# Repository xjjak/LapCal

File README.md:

[![CC BY-NC-SA 4.0][cc-by-nc-sa-shield]][cc-by-nc-sa]

# LapCal

*by Emil² - Ξ*

Building gloves that enable typing on a 34-key keyboard without an actual physical keyboard using IMUs and machine learning. 

This work is licensed under a
[Creative Commons Attribution-NonCommercial-ShareAlike 4.0 International License][cc-by-nc-sa].

[![CC BY-NC-SA 4.0][cc-by-nc-sa-image]][cc-by-nc-sa]

[cc-by-nc-sa]: http://creativecommons.org/licenses/by-nc-sa/4.0/
[cc-by-nc-sa-image]: https://licensebuttons.net/l/by-nc-sa/4.0/88x31.png
[cc-by-nc-sa-shield]: https://img.shields.io/badge/License-CC%20BY--NC--SA%204.0-lightgrey.svg

## Attributions

For the ring CAD models in OpenSCAD we use the [Round-Anything library by Irev-Dev](https://github.com/Irev-Dev/Round-Anything), which is licensed under the MIT License.

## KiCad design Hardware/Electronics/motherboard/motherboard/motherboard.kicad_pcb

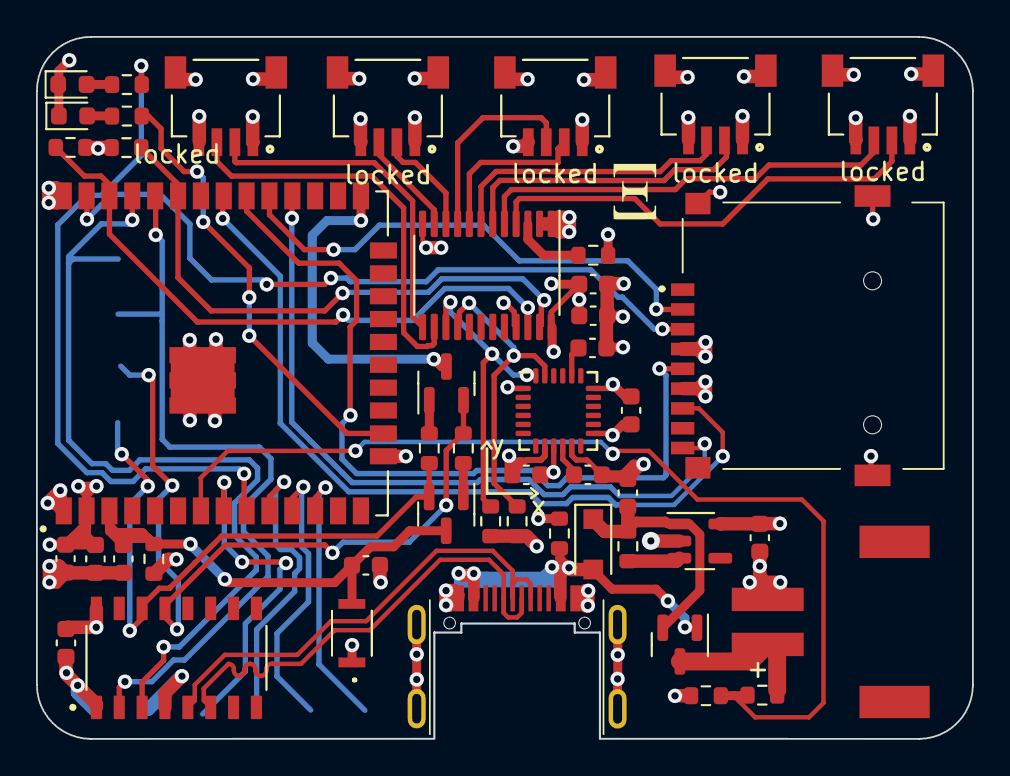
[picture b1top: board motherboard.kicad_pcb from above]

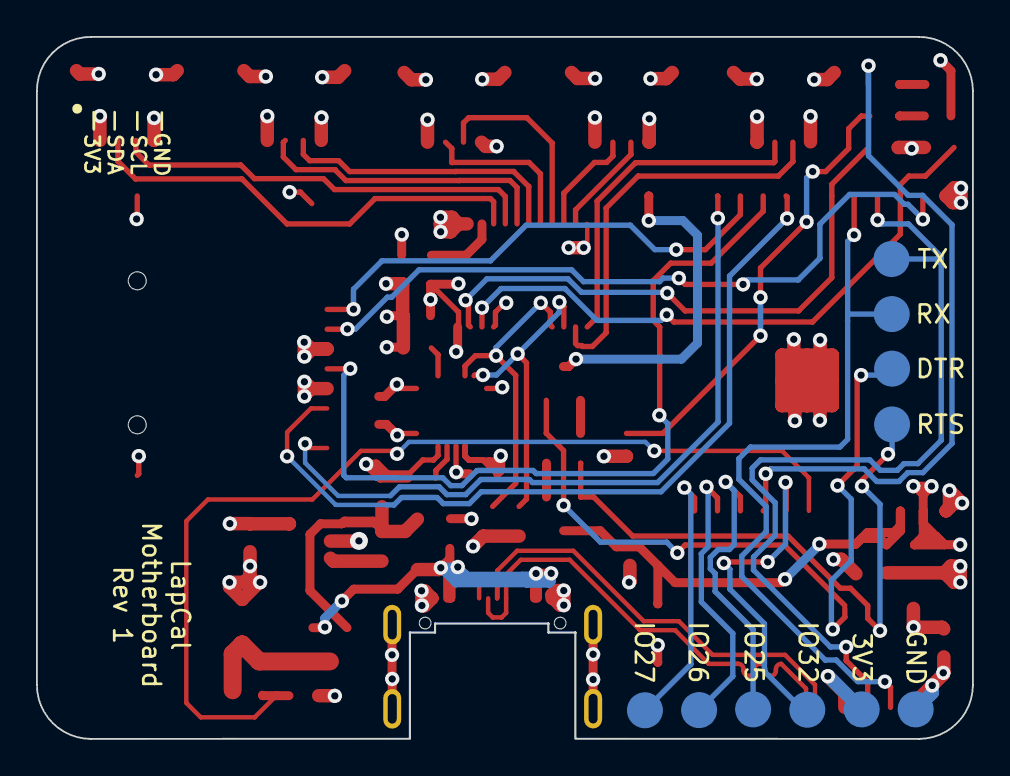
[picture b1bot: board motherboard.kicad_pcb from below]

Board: 4 copper layers, 52.0 x 39.0 mm, 57 parts (10 on the bottom side), 47 nets.

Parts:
111: TF-01A; TF01A
C1, C2, C5, C8, C10, C11, C13: 0.1uF; C_0603_1608Metric
C3, C4: 1uF; C_0603_1608Metric
C7: 22uF; C_0603_1608Metric
C9: 10uF; C_0603_1608Metric
C12: 10nF; C_0603_1608Metric
C14: 2.2nF; C_0603_1608Metric
D1: mbr120; D_SOD-123F
D2: blue; LED_0603_1608Metric
D3: green; LED_0603_1608Metric
J1: USB_C_Receptacle; TYPE-C-31-M-14
J3, J4, J5, J6, J7: locked; JST_SM04B-SRSS-TB(LF)(SN)
J8: Conn_01x02_Female; HX25003-2AWB
Q1: HXY3401AI; SOT-23
Q2, Q3: MMBT3904; SOT-23
R1, R3, R4, R5: 10k; R_0603_1608Metric
R2, R8, R9: 100k; R_0603_1608Metric
R6, R10: 5k; R_0603_1608Metric
R7: 7k; R_0603_1608Metric
R11, R12: 3.7k; R_0603_1608Metric
R13, R14: 4k7; R_0603_1608Metric
S1: TS2306A-240GF-MSM-9_C388290; TS2306A240GFMSM9_C388290
TP3: IO26; TestPoint_Pad_D2.0mm
TP8: RX; TestPoint_Pad_D2.0mm
TP9: DTR; TestPoint_Pad_D2.0mm
TP10: RTS; TestPoint_Pad_D2.0mm
U1: ESP32-WROOM-32E_(16MB); XCVR_ESP32-WROOM-32E_(16MB)
U2: AP2112K-3.3; SOT-23-5
U3: CH340C; SOIC127P600X180-16N
U4: TCA9548APWR; TSSOP-24_4.4x7.8mm_P0.65mm
U5: MPU-6050; InvenSense_QFN-24_4x4mm_P0.5mm
locked: 3V3; TestPoint_Pad_D2.0mm
locked#2: IO32; TestPoint_Pad_D2.0mm
locked#3: TX; TestPoint_Pad_D2.0mm
locked#4: IO27; TestPoint_Pad_D2.0mm
locked#5: IO25; TestPoint_Pad_D2.0mm
locked#6: GND; TestPoint_Pad_D2.0mm

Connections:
+3V3: 111.4, C4.1, C5.1, C7.1, C8.1, C9.1, C10.1, C11.1, C12.1, J3.1, J4.1, J5.1, J6.1, J7.1, R1.1, R7.1, R11.1, R12.1, R13.1, R14.1, U1.2 (3V3), U2.5 (VOUT), U3.4 (V3), U3.16 (VCC), U4.24 (VCC), U5.8 (VDDIO), U5.13 (VDD), locked.1
+3V8: J8.1, Q1.3 (D), R8.1
CS: 111.2, U1.29 (IO5)
D+: J1.A6 (D+), J1.B6 (D+), U3.5 (UD+)
D-: J1.A7 (D-), J1.B7 (D-), U3.6 (UD-)
DTR: Q2.2 (E), R4.1, TP9.1, U3.13 (~DTR)
EN: C1.2, C2.1, Q3.3 (C), R1.2, S1.2, U1.3 (EN)
GND: 111.6, 111.MP2, 111.MP3, 111.MP4, C1.1, C2.2, C3.2, C4.2, C5.2, C7.2, C8.2, C9.2, C10.2, C11.2, C12.2, C13.2, C14.2, D2.1 (K), D3.1 (K), J1.A1 (GND), J1.A12 (GND), J1.B1 (GND), J1.B12 (GND), J1.S1 (SHIELD), J3.4, J3.S1 (SHIELD), J3.S2 (SHIELD), J4.4, J4.S1 (SHIELD), J4.S2 (SHIELD), J5.4, J5.S1 (SHIELD), J5.S2 (SHIELD), J6.4, J6.S1 (SHIELD), J6.S2 (SHIELD), J7.4, J7.S1 (SHIELD), J7.S2 (SHIELD), J8.2, R2.2, R9.2, S1.1, U1.1 (GND), U1.15 (GND), U1.38 (GND), U1.39_1 (GND), U1.39_2 (GND), U1.39_3 (GND), U1.39_4 (GND), U1.39_5 (GND), U1.39_6 (GND), U1.39_7 (GND), U1.39_8 (GND), U1.39_9 (GND), U2.2 (GND), U3.1 (GND), U4.1 (A0), U4.2 (A1), U4.12 (GND), U4.21 (A2), U5.1 (CLKIN), U5.9 (AD0), U5.11 (FSYNC), U5.18 (GND), locked#6.1
GPIO0: Q2.3 (C), U1.25 (IO0)
I2C1_SCL: R11.2, U1.36 (IO22), U4.22 (SCL)
I2C1_SDA: R12.2, U1.33 (IO21), U4.23 (SDA)
IO13: R6.1, U1.16 (IO13)
IO25: U1.10 (IO25), locked#5.1
IO26: TP3.1, U1.11 (IO26)
IO27: U1.12 (IO27), locked#4.1
IO32: U1.8 (IO32), locked#2.1
IO33: R10.1, U1.9 (IO33)
IO35: R8.2, R9.1, U1.7 (IO35)
MISO: 111.7, U1.31 (IO19)
MOSI: 111.3, U1.37 (IO23)
unnamed: C3.1, D1.1 (K), Q1.2 (S), R5.2, U2.1 (VIN)
unnamed: C13.1, U5.10 (REGOUT)
unnamed: C14.1, U5.20 (CPOUT)
unnamed: D2.2 (A), R6.2
unnamed: D3.2 (A), R10.2
unnamed: Q2.1 (B), R3.2
unnamed: Q3.1 (B), R4.2
unnamed: R5.1, U2.3 (EN)
unnamed: R7.2, U4.3 (~RESET)
Onboard_SCL: R14.2, U4.16 (SC5), U5.23 (SCL)
Onboard_SDA: R13.2, U4.15 (SD5), U5.24 (SDA)
PROG_RX: U1.35 (TXD0), U3.3 (RXD), locked#3.1
PROG_TX: TP8.1, U1.34 (RXD0), U3.2 (TXD)
RTS: Q3.2 (E), R3.1, TP10.1, U3.14 (~RTS)
SCLK: 111.5, U1.30 (IO18)
SD_DETECT: 111.CD1, U1.28 (IO17)
Sense1_SCL: J3.3, U4.5 (SC0)
Sense1_SDA: J3.2, U4.4 (SD0)
Sense2_SCL: J4.3, U4.7 (SC1)
Sense2_SDA: J4.2, U4.6 (SD1)
Sense3_SCL: J5.3, U4.9 (SC2)
Sense3_SDA: J5.2, U4.8 (SD2)
Sense4_SCL: J6.3, U4.11 (SC3)
Sense4_SDA: J6.2, U4.10 (SD3)
Sense5_SCL: J7.3, U4.14 (SC4)
Sense5_SDA: J7.2, U4.13 (SD4)
VBUS: D1.2 (A), J1.A4 (VBUS), J1.A9 (VBUS), J1.B4 (VBUS), J1.B9 (VBUS), Q1.1 (G), R2.1

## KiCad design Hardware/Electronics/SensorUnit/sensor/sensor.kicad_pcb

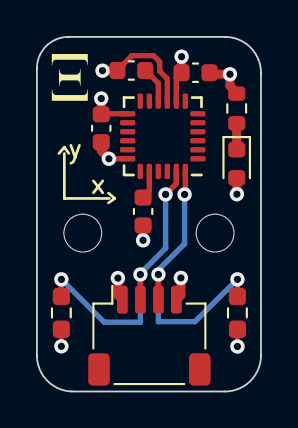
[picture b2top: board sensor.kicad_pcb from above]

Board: 4 copper layers, 12.4 x 19.7 mm, 12 parts (0 on the bottom side), 7 nets.

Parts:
C1, C2: 0.1uF; C_0603_1608Metric
C3: 2.2nF; C_0603_1608Metric
C4: 10nF; C_0603_1608Metric
D1: Blue; LED_0603_1608Metric
H1, H2: MountingHole; MountingHole_2.1mm
J1: SM04B-SRSS-TB(LF)(SN); JST_SH_SM04B-SRSS-TB_1x04-1MP_P1.00mm_Horizontal
R1: 2k; R_0603_1608Metric
R2, R3: 4k7; R_0603_1608Metric_Pad0.98x0.95mm_HandSolder
U1: MPU-6050; InvenSense_QFN-24_4x4mm_P0.5mm

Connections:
+3V3: C2.1, C4.1, D1.2 (A), J1.4, R2.1, R3.1, U1.8 (VDDIO), U1.13 (VDD)
GND: C1.2, C2.2, C3.2, C4.2, J1.1, R1.1, U1.9 (AD0), U1.18 (GND)
unnamed: C1.1, U1.10 (REGOUT)
unnamed: C3.1, U1.20 (CPOUT)
unnamed: D1.1 (K), R1.2
SCL: J1.2, R3.2, U1.23 (SCL)
SDA: J1.3, R2.2, U1.24 (SDA)

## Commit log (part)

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2023-11-17 Moved ip address to a constant
2023-11-17 Make touch recognition touch identifier based
    This uses the internal identifier for every touch to map each touch to
    a certain position. These positions are only logged at the start of
    the touch. Thus the drawing and the end log message depend on the
    start touch position and most releases are recognised properly.
2023-11-18 Added TIMING macro to enable and disable time breakpoints
2023-11-18 Added outputs from serial monitor as timing data sets
2023-11-18 Changed task callback parameter back to pvParameters for clarity
2023-11-18 Added more timing output points, including time for all readings and time spent in the rest of main loop
2023-11-19 Added picture of prototype to README
    Made the concept drawing smaller and added a picture of the protoype
    next to it as a sort of side-by-side comparison to show the current
    status better and prettifying the README.
2023-12-08 Added missing key identifiers
    Some possible keys were not handled in the `prepare_dataset.py` script.
2023-12-11 Added `Model` class with implementations for sklearn and tf
    The two implementations are rather rudimentary but should work most of
    the times.
2023-12-16 Abstracted button checks
    This change adds an abstraction `onButtonClick` for the classical
    button clicked, do action combination.
2023-12-17 Let server set its own send back ip
    The server will determine its own ip and set it in the javascript code
    instead of just a constant in the js code.
2023-12-17 Changed build partition to min_spiffs.csv
    Adding the BLESerial library made the program to big so pio threw an error. This could be fixed by changing the partition config to min_spiffs.csv, which reduces the size allocated for a file system 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
2024-01-19 SD setup now after sensors setup
2024-01-22 Avoid unusable stand-alone data
    In some datasets there the virtual keyboard has some data recorded
    before the board could collect the respective data from the sensors.
    This is generally not a big problem as this data is discarded when the
    dataset is preprocessed but it could theoretically cause some strange
    data in the beginning and clutter the joined ascii output.
    Additionally, this commit includes a newer version of the
2024-02-02 Remove ble setup line
    Removed leftover artifacts of BLE setup.
2024-02-09 Added environments in platformio.ini for different hands
    In two different environments "left" and "right" the build_flag "RIGHT_HAND" is passed to the pre-compiler using "build_flags= -D RIGHT_HAND=[0/1]".
2024-02-11 Added local datasets and corresponding descriptions
    Some of the used datasets were lingering here locally, even though
    they should have been pushed some time ago already. Further, to
    increase transparency I try to abide by the policy to add a somewhat
    meaningful description and the introducton date to every dataset.
2024-02-12 Value negation to mirror left hand
    If RIGHT_HAND is set to 1 the following values will be negated:
    - x & y accel
    - y & z rotation
2024-02-13 Adding data folder for collected datasets
2024-02-15 Add script that loops printing unix timestamp
2024-02-15 Side by side comparison of timestamps
    Set of value pairs the timestamp on the host computer being collected as each line comes in on the serial monitor.
    There is also a simple evaluation script that prints the mean and then standard deviation of the microseconds, which is less than 1ms.
2024-03-01 First draft of visualization tool
    This is simple implementation with the proposed interface from
    https://github.com/xjjak/LapCal/issues/39.
    The implementation is quite simple and the window is fragile as it
    only draws every time when it receives an input. But it should
    suffice for our purposes.
2024-03-01 Added gitignore for data folder
2024-03-01 Documentation updates (#35)
    * Moved pictures to new images folder
    * Adding data folder for collected datasets
    * Adding webpages folder with two websites printed to pdf
    * Reverting webpages and data folder addition
    This reverts commit 513af0b638e81bd35da1c43c63645ae0be84f067 and
    e5f14b9c60bcb5304f2e2aae4c3e6bdbffd16a22.
2024-03-01 Added build flag MULT_CORE
    MULT_CORE is set to 1 by default (if not defined), enabling
    parallelization. MULT_CORE=0 disables it.
2024-03-13 Provisoric transmission over BLE Serial
    Build flag works, but doesn't exclude the BLESerial library when not
    needed.
2024-03-17 Build flag BLE_SERIAL fully functional
    Build flag is now functional and if not set, the library is not
    included.
    The library is now also added via platformio.ini instead of locally.
    The `ble.begin()` call includes the options that enable the builtin led
    (pin 13), and name the device "lapcal [left/right]" depending on the
    hand set.
2024-03-18 Update README.md
    Indented optional steps in QMK firmware mods
2024-03-18 Add link to hid_listen to README
2024-03-18 PlatformIO environments for ble-serial
    The two environments `left-ble` and `right-ble` were added, appending
    the build flags `MULT_CORE=0` and `BLE_SERIAL=1`.
2024-03-19 Init Software README
2024-03-19 Update structure diagram
    Make the processes more elaborate and up to date (i think).
2024-03-22 Check for global hid_listen and make local script location relative
    Calling the `keylogger-for-data-collection.sh` script from another
    directory will result in an error because the local hid_listen script
    will not be in that directory. Referring to the hid_listen script
    from the keylogger script location (dirname "$0") solves this issue.
    Further checking for a global hid_listen script makes things easier
    with a nix-shell environment.
2024-03-23 Removed placeholder comment
2024-03-23 Reformat README.org to README.md
    All README.org files were reformatted to README.md files to ensure
    consistency.
    Since one of them mentioned the nix environment that one is also
    already included in this commit.
2024-03-24 Fix broken images
2024-03-25 Timestamp output from mobo now in unix time
    Instead of outputting the microseoconds since boot, the full
    unix_timestamp is now used in inaccurate microseocond resolution since
    only millisconds are read from ntp server.
2024-03-27 further click detection clean up
2024-03-28 working presentation
2024-04-25 First draft of all rings
    Created a ring module that takes the finger diameter and optionally a
    tolerence and an angle at which the center of the hole is shifted to.
    With this five rings for each individual finger were added easily. What
    is missing are the fillets and correct parameters.
    Another thing that could be improved is the way the SenseUnit slot is
    attached to the ring. When the diameter of the outer contour of the ring
2024-04-27 Remove outdated comments
2024-05-01 Add simple configuration mechanism
    This commit does a few things:
    1. Introduce `configuration.rkt` which handles all the logical
    structure concerning configuration management. It provides
    `load-config` and `write-config` to load and write configurations
    to a provided file path. Additionally, is provides
    `generate-default-config` and `get-attribute`; the former is only
2024-05-10 Removed local plugin location
2024-05-10 Added Round Anything library as submodule for fillets
2024-05-10 Improved attribution of Round-Anything
2024-05-10 Lowercase 'ring' in readme
2024-05-12 Relocate READMEs to respective directory
    Module documentation should be local to their respective
    directories. Before it was all collected in the `lib/` directory which
    has sub folders for every framework it provides modules for. The
    framework specific module documentation was moved to these sub folders.
2024-05-12 Add docstrings to metric.py (tensorflow)
    Finished adding the docstrings to the custom tensorflow module `metric.py`.
2024-05-12 Add .gitignore for the software directory
2024-05-12 Add first draft of model structure
    This is the current idea on how to structure the models.
    Only problem with current design is the ugly way we load the libraries.
2024-05-12 Remove .envrc file
    .envrc files are for private use only. It was merely pushed by mistake.
2024-05-19 Tolerance actually affects size now and is roughly adjusted
2024-05-25 Fix misspelled directory name
2024-08-05 Add descriptive comment
2024-09-02 Restructure source code and add command line arguments
    Source code is now separated into two subfolders:
    - `src`, which contains all the regular code until now, and
    - `test`, which is currently empty (and thus not in the git
    repository) which will encapsulates future tests.
    Further, a starting script `run.sh` was added along with support for
    command-line arguments:
2024-10-05 Binary data transmission over ble prototype with single imu
2024-10-12 ignore emacs related files for mainboard development
2024-10-12 Improve formatting and remove single cycle timing
2024-10-12 Updated ocumentation in readme
2024-10-12 Add documentation for ble-receiver script
2024-11-03 Fix bugs in `ble-serial.rkt`
    Fixed some minor edge case bugs that disabled ui elements even though
    they should still be available. Also added some more comments.
2024-11-05 Make consistent of use of spaces for indentation
2024-11-06 README clarifications, added section on setting build flags
2024-11-06 ble-receiver: prettier scan output
2024-11-18 Firmware: Start advertising on disconnect
    Advertising (showing up and able to be connected to as a BLE device) is
    now started again after a disconnect. Now the device doesn't need to be
    reset after a ble disconnect, but can be immediately be connected to
    again.
2024-11-18 Firmware: hand (left/right) shows up in now lowercase ble name
    The name of the BLE Server now depends on the hand. As added to the
    README:
    - left: `lapcal left`
    - right: `lapcal right`
    and is now also fully lowercase.
2025-01-07 Add timestamp-analysis.org file for scripts
    Contains data collection block and rudimentary analysis, using
    org-babel. 2 first results are included.
2025-01-11 Sweep binary output of middle finger column
2025-01-13 Non-functional Elite-C (ATmega32u4) firmware for collecting key events
    Firmware itself should be functional, but neither SoftwareSerial nor
    HardwareSerial on designated, but not really free works with the
    mainboard, probably because of the necesary level-shifter. May be faulty
    hardware.
2025-01-15 Bug live-plotting: Changing plot min/max
    When changing min/max values of the plot, the other one(s) got reset to
    the default value. This was fixed by setting the int-[min/max/size]
    variable to the new value upon update. Before it stayed at the default
    value and got used if one of the other fields got updated.
2025-01-15 Add terminating sequence to data packet
2025-01-15 Preliminary data set records with first two data sets
2025-01-19 Readme org shield fix
2025-01-19 complete licensing boilerplate
2025-01-25 README: Fix license link
2025-03-10 Exempt `Software/_dataset` folder from version control
2025-03-11 Add feature aggregation
2025-03-13 Software: readme - add structure diagram + missing diagram files
2025-03-16 Software: readme - fix format example & reorder
2025-03-17 Add centering using EMA
2025-03-17 Amend title
2025-03-23 Firmware: add sweep-data-collection-setup folder
2025-03-23 sweep-data-collection-setup: rename firmware folders
2025-04-04 Update `Software` gitignore to exclude ob-jupyter files
    To execute the code in the org files, we use ob-jupyter which
    sometimes creates auxiliary and output files in a local directory
    `.ob-jupyter`. These are mostly temporary and all persistent output
    files should have explicit output locations.
2025-04-07 org-readme: Add Structure section
2025-04-07 org readme: Add modular concept image
2025-04-07 Software readme: Add usage section about development setup
2025-04-07 Software readme: fix src block example
2025-04-07 org readme: delete old md readme
2025-05-14 data-collection: Migrate to pandas dataframes
2025-06-21 machine-learning: Some simple prediction tests
2025-06-22 machine-learning: Add window-based naive prediction strategy
    This commit mainly adds a third strategy for the naive prediction
    idea which uses a rolling window to compute the maximal difference
    between maximum and minimum of the window.
    This commit also improves upon the loading code block which now also
    supports choosing the stage to load if the user uses a prefix
    argument.
2025-07-17 machine-learning: Init CNN approach & data preparation
2025-07-17 machine-learning: Add data loader
